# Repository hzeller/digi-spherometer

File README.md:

A Digital Spherometer
=====================

Converting the sagittal measurement (SAG) from a dial indicator and converting
in your head to a sphere radius is a pain.

This project uses a microcontroller to make this more pleasent: it reads out
the digital indicator and converts the reading to a sphere radius value
printed on an OLED display. It also adds some other nifty features, such as
converting this into the ƒ/N for your mirror size. See [firmware]-page for
feature details.

The microcontroller is an [ATTiny85], the display is a 0.96" [SSD1306], or
1.3" [SH1106] compatible 128x64 OLED display with I²C interface.

Supported dial indicators are [Mitutoyo 543] (good, industry-standard quality)
and a generic [autoutlet-indicator] (relatively cheap, has 1μm resolution but
no documented accuracy figures. Sells under many different names).

The [case](./frame) to hold the dial indicator, microcontroller+display and
batteries is 3D-printed, the base can be laser-cut or machined from some metal
plate.

### Quicklinks

Case | Electronics | Firmware | Calibration
-----|-------------|----------|-------------
 |  |  | 

### User Manual

Like any Spherometer, we first need to zero the device on a reference surface.
Typically this is done on a flat surface plate, so this spherometer allows for
that: place it on a flat surface and set the dial indicator to zero.

Unlike other spherometers, this device also allows for another (experimental)
mode: using the grinding tool as a reference surface. The convex shaped tool
has the same (but inverted) curvature as the mirror, so this can be used
as a reference, if the tool and mirror are already sufficiently mated. The
spherometer then can do the math to derive the value from that.

To use that mode, place the spherometer on the tool (make sure the balls and
indicator rest on the tiles not hitting a seam), and zero the dial indicator.
The arrow-shaped button the right side of the display allows to toggle between
the reference mode. The selected mode is highlighted.

Reference on Surface Plate         | Reference on Tool               |
-----------------------------------|---------------------------------|
  | 

The tool reference is probably a bit less accurate, but it does not require
you to be in posession of a flat surface plate.

After the device is zeroed, place it on the mirror. It now shows all relevant
values on one screen. This is what you see from top to bottom:

 * The ƒ/N value for a given mirror size. The mirror size (chosen here: `⌀8"`)
   can be cycled through from a list with the arrow-button.
 * The focal length including error margins derived from dial-indicator error
   and spherometer leg-radius error.
 * The radius is shown in a large font

On the bottom left you see a symbol indicating which reference surface this
was against. There are two symbols indicating flat surface and tool referenced
(same symbols as used in the zero screen).

Millimeter | Inch |
-----------|------|
 | 

So in this example we see in one screen, that this is a mirror with a radius
of about 2482mm, a focal length of 1241mm which is ƒ/6.11 for this
8" mirror. The reference surface was a flat surface plate.

Switching between metric and inch on the dial indicator automatically
switches the calculated values to the corresponding units.

The device does not need an additional power button: it auto-detects
when the drop-indicator is switched off and goes to sleep.

[attiny85]: https://www.microchip.com/wwwproducts/en/ATtiny85
[ssd1306]: https://www.ebay.com/sch/i.html?_nkw=ssd1306+i2c+128x64
[sh1106]: https://www.ebay.com/sch/i.html?_nkw=sh1106+i2c+128x64
[Mitutoyo 543]: https://www.mitutoyo.com/products/small-tool-instruments-and-data-management/indicators/digimatic-indicators/absolute-digimatic-indicator-id-s/
[autoutlet-indicator]: https://www.amazon.com/gp/product/B07C63VFN3
[avr-gcc]: https://gcc.gnu.org/wiki/avr-gcc
[firmware]: ./firmware/README.md

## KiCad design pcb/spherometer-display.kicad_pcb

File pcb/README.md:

Electronics
===========

Schematic is pretty straightforward, mostly things are wired up directly
to the Attiny85. Level conversion of the 1.5V signals from the indicator is
done with some generic NPN transistors.

Some dial indicators, such as Mitutoyo, already have an open collector output,
in that case, the jumpers allow to directly connect the device. The
`R1`, `R2`, `Q1`, `Q2` components need not be populated in that case.

There are two slot connectors on the board, on one side to connect the indicator
(GND, CLK and DATA and optional 1.5V), the other to connect the battery. The
placement is in accordance with the 3D-printed cases.
The connectors are slots to allow for a convenient, low-profile soldering of
wires to it (wires vanish completely inside the slots).
At the top there is some space for easier wire-management (see picture below).

Some indicators (such as the autoutlet) can be powered from an external 1.5V
source; if the battery-pack is tapped in the middle, this is passed through.
Do not use at this point, leave the 1.5V slots disconnected: turns out that the
long battery wire and the connection to the μC injects too much noise. Might
need some filtering.

The board is designed with cut-outs to stay clear of components on the
particular display module I was using to place the board with no gap on the
module; YMMV.

### BOM

Count  | Part                     | Footprint          | Designators  | Remarks
-------|--------------------------|--------------------|--------------|---------
1      | Attiny85V-10             | SOIC-8 5.3mm wide  | U1           |
1      | Capacitor 100n           | 0603 (1608 Metric) | C1           |
3      | Resistor 47k             | 0603 (1608 Metric) | R1, R2, R3   |
2      | MMBTA06LT1HTSA1          | SOT23              | Q1, Q2       | Any SOT23 NPN will do
1      | Panasonic EVQ-P7L01P     | (custom)           | SW1          |
1      | SH1106 Display (i2c)     | (custom)           | Disp         |

Then of course a 1.3" SH1106 module with I²C interface. Make sure the pins
come in sequence `SDA`, `SCL`, `VCC`, `GND` if looked from the back.

### Schematic

### PCB
This board is soldered to the back of a 1.3" OLED display

Also [shared here on OshPark](https://oshpark.com/projects/MvLMlrob); to keep
things thin, order with 0.8mm thickness.

### View through acrylic bottom

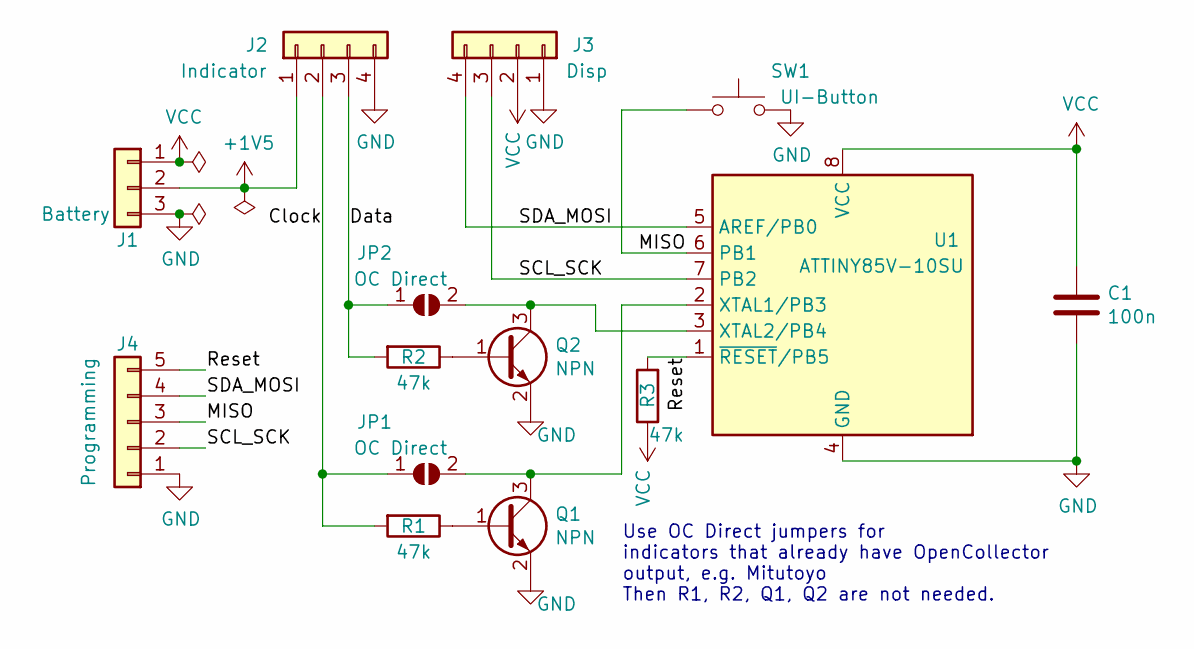
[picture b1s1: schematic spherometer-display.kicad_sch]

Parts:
C1: 100n; C_0603_1608Metric
J1: Battery; connect-edge-3slot-2mm
J2: Indicator; connect-edge-4slot-2mm
J3: Disp; PinHeader_1x04_P2.54mm_Vertical
J4: Programming; PinHeader_1x05_P2.54mm_Vertical
JP1, JP2: OC Direct; SolderJumper-2_P1.3mm_Open_RoundedPad1.0x1.5mm
Q1, Q2: NPN; SOT-23
R1, R2, R3: 47k; R_0603_1608Metric
SW1: UI-Button; EVQP7-Switch
U1: ATTINY85V-10SU; SOIC-8_5.23x5.23mm_P1.27mm

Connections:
+1V5: J1.2, J2.1
/Clock: J2.2, JP1.1 (A), R1.2
/Data: J2.3, JP2.1 (A), R2.2
/MISO: J4.3, SW1.2, U1.6 (PB1)
/Reset: J4.5, R3.2, U1.1 (~RESET/PB5)
/SCL_SCK: J3.3, J4.2, U1.7 (PB2)
/SDA_MOSI: J3.4, J4.4, U1.5 (AREF/PB0)
GND: C1.2, J1.3, J2.4, J3.1, J4.1, Q1.2 (E), Q2.2 (E), SW1.1, U1.4 (GND)
unnamed: JP1.2 (B), Q1.3 (C), U1.2 (XTAL1/PB3)
unnamed: JP2.2 (B), Q2.3 (C), U1.3 (XTAL2/PB4)
unnamed: Q1.1 (B), R1.1
unnamed: Q2.1 (B), R2.1
VCC: C1.1, J1.1, J3.2, R3.1, U1.8 (VCC)

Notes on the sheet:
Use OC Direct jumpers for indicators that already have OpenCollector output, e.g. Mitutoyo Then R1, R2, Q1, Q2 are not needed.

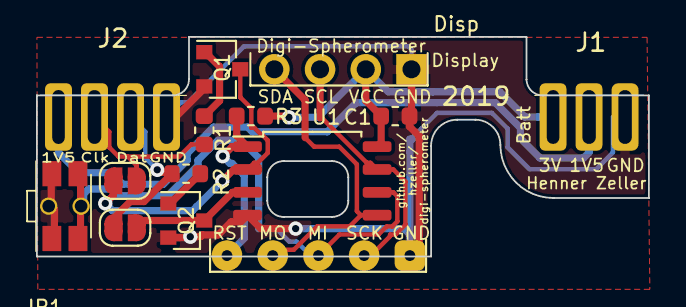
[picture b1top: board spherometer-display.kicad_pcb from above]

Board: 2 copper layers, 34.0 x 12.2 mm, 14 parts (0 on the bottom side), 13 nets.

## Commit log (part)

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2019-02-23 Basic support for ssd1306 display with compiled-in fonts.
    o Provide a i2c master that works with ATTiny devices.
    o initialize SSD1306 display and allow to write blocks from
    PROGMEM. There is not enough space for a full frame-buffer
    in the ATTiny.
    o some basic generated compiled-in font in PROGMEM; generated
    from some BDF font.
2019-02-24 Provide a ClearScreen();
2019-02-24 Document that SSD1306 can deal with faster data rate.
2019-02-24 Read sag from digital gauge and output radius. First version.
    o Dial gauge uses a very simple serial clock/data protocol transmitting
    24 bits. First 20 bits are the value followed by a sign bit. Last
    bit is a non-metric flag.
    o Reading that and also doing some simple 'gauge is off' detection
    which kicks in when the clock stops transmitting (data is sent
    about 10 times/second)
2019-02-24 Update missing glyphs for updated UI. Add sleep mode on indicator off.
    o Update needed characters in fonts for all necessary elements of the UI.
    o When we detect the dial indicator stop clocking data (i.e. it is
    switched off), go to sleep. We still draw about 10μA, but that is
    mostly due to the OLED display. Disconnecting the OLED from GND
    makes current consumption drop to 0.8μA. Maybe add another transistor
    to disconnect OLED ?
2019-02-24 Be more conservative waiting for display power on.
    Waiting 100ms does not seem to work well for a slow ramping up
    power source. Make that 500ms.
    Also provide a Reset() function to reset display after sleep.
2019-02-24 Clean up header.
2019-02-24 Start README.
2019-02-24 Add .gitignore
2019-02-24 Image: Showing the system 'on the bench'
2019-02-25 Move "OK" characters into separate font; add ƒ character to smalltext.
    o The OK characters were forcing the array size for all fonts to be very big,
    so separating that out makes the bignumber font use a lot less memory.
    o add ƒ character to smalltext; want to use it for some focal length display.
2019-02-26 Move dial indicator reading to inline definition in include file.
2019-02-26 Round value instead of truncating.
2019-02-26 Round values. Make things const where possible. Fix indentation.
2019-02-26 Prepare data for ƒ page. Uses more memory, but not pressing right now.
2019-02-26 Simplify interface: have strfmt() format into a statically allocated buffer.
    Instead of passing a buffer to the strfmt() call, have it use some statically
    allocated internal buffer. Of course, this limits the use to a single
    format at a time ... but that is anyway what we're doing :)
    This increases readability (less parameters to pass) and is totally
    fine for this embedded use-case.
    Also saves 8 bytes of code :)
2019-02-26 Add a page that shows focal lengths and ƒ-number for selected mirror sizes. Choose with button.
    A button allows to rotate between three pages: the regular page showing the radius and
    two pages showing the focal lengths (=radius/2) and a choice of ƒ-numbers calculated
    for common mirror sizes. We show 6 different mirror sizes on two pages.
    Also here, we support metric and imperial, depending on the dial setting.
    Choice of metric sizes is {150mm, 200mm, 250mm, 300mm, 400mm, 600mm}, and
    the corresponding imperial sizes are {6", 8", 10", 12", 16", 20"}.
2019-02-26 FillEndOfStripe() is now functionally more a FillStripeRange(). Rename.
2019-02-27 Allow for 'wiggle' room for 'flat'.
    Sometimes the dial will hover around zero +/- 1 count. Let's just
    assume this to be flat.
    Also, rename the reading, the 'value', to 'abs_value' to better
    reflect the range we expect.
2019-02-28 SSD1306: compile time choice if upside down.
2019-03-01 Add a screw-on battery lid.
2019-03-01 Add embedded nuts in print.
2019-03-01 Add prototype pictures in README.
2019-03-03 Add laser-cut pattern for the leg-holding acrylic base.
2019-03-03 Get rid of the display base. We let the bottom transparent.
2019-03-03 Add schematic.
2019-03-08 Make a 'wiggly' battery back. Looks nicer, but also harder to print.
2019-03-09 Add nut-channels everywhere, so that they can be put in after the print.
    Also: add README and Makefile in frame/ directory.
2019-03-09 Move development picture to the firmware README.
2019-03-09 Less text on main-README, point to firmware README for details.
2019-03-10 Add a battery pictogram in the battery box.
2019-03-10 Add git-hash print to hidden part of 3D print (for easier later re-print).
    To be able to re-print a part with exactly the given version, add a
    git-hash number and date of the *.scad file in the final output model.
2019-03-10 Add center mount hole to the base-plate. Update images.
2019-03-11 Add a champfer on the top right/left edges of the Battery box.
    Also add a couple of TODOs. Remove the sideways channel for the cable,
    it should go down the back for easier routing.
2019-03-12 Cable management: run indicator data lines on the back.
2019-03-13 Move git-hash from bottom to inside; simplify top clearance.
    The bottom should be as flat as possible for mounting, and we only
    need the git-hash when re-printing something, so inside is perfectly
    good.
2019-03-13 Add groove for 1.5V cable.
2019-03-13 Make top cut-out a bit more 'organic' with a cos()-swing.
2019-03-15 First hacky way to add display holder..
2019-03-16 Fix todo: use display_high parameter properly.
    Also: add secondary front-edge champfer.
2019-03-16 switch off wiggle-back by default (hard to print)
2019-03-22 Code reduction: make I2C master just a bunch of static methods.
2019-03-30 Swap clk/data in new board. Do pull-up inside.
2019-03-30 Hack in support for SH1106; needs cleanup.
2019-03-30 Shorten splash-screen to fit with wider fonts.
2019-03-31 Move DISP_SH1106 define to Makefile.
    Also, somewhat unrelated, make UTF8 iterator only require prefix++.
2019-03-31 Update prototype image.
2019-03-31 back bottom mounting hole: put nut in from top not battery case.
2019-04-02 Only use SH1106 subset of OLED functionality: more compatible.
2019-04-02 Factor out common calls in SH1106 display to save code.
2019-04-02 Add missing image.
2019-04-05 Widen battery wire hole. Fix indentation.
2019-04-05 Make mounting hole through squeeze-block optionsl.
2019-04-06 Make cable-channels more configurable.
    o Bottom clearance.
    o distance from center.
    o width.
2019-04-08 Adjust display box to fit current larger display.
2019-04-21 Fix relative include to generating stl files.
2019-04-21 Update schematic picture.
2019-04-28 Prepare to be usable with dial indicators that already provide OpenCollector output.
    Add a solder-jumper that allows to directly wire the indicator directly to Attiny.
2019-04-28 Route board; add Makefile to create fab files.
2019-04-28 Update renderings.
2019-04-28 Make bounding box around programming header more compact.
2019-04-28 Re-add OSHW symbol (it got lost as it was not locked).
2019-05-07 Fix: Attiny85 is the huge 5.3mm SOIC-8 footprint.
2019-05-08 Update PCB rendering with larger SOIC-8 footprint that the Attiny has.
2019-05-09 Add EVQP7 switch. It is more sturdy than EPAV.
2019-05-10 Connect indicator and battery with low-profile slot cable solder connects.
2019-05-11 Some cleanup. Also add cut-outs to clear components on SH1106 display back.
2019-05-11 DFM: Add fillets to inner cut-out
2019-05-11 Put programming header legend also on back of board.
2019-05-11 Clarify required pin-sequence of SH1106.
2019-05-11 Un-hide signal layers.
2019-05-11 OshPark uses 1.73mm mill for inner cut-outs; so use 0.9mm radius for shape.
2019-05-16 Adapt case to new PCB. This involves an integrated button.
2019-05-16 Update rendering.
2019-05-16 Remove display side-screws.
2019-05-16 Update case rendering.
2019-05-17 Add ajdustment knob how close the display-case comes to edge.
2019-05-17 Experiment with inverse font display (not for now, display goes dim)
    Other than that: smallish
    o Use diameter symbol for mirror diameter. Not sure if good yet.
    o make sure display is clear-screened when re-switching on the
    indicator while the 'outro' is still shown.
2019-05-17 Align ƒ= text with r= text.
2019-05-17 Update firmware documentation readme.
2019-05-20 Update list of generated fab files.
2019-05-20 Update PCB image.
2019-05-21 Update display image.
2019-05-21 Include UI image in firmware README.
2019-05-21 Slightly nicer crop for oled.
2019-05-21 Left align N-number; provide a little more space for aperture size.
2019-05-23 Link to README.md's directly instead of directories.
    This is more mobile-friendly.
2019-05-25 Make radius a -D-efinable parameter.
2019-05-25 Add calibration description.
2019-05-25 Add a sample calibration scan.
2019-05-25 Add link to calibration page.
2019-05-26 Add more options how to calibrate.
2019-05-26 Make tactile dome poke out a little more.
2019-06-01 Add a tool reference mode.
    When zero-ing, we now can choose between a flat surface and 'tool reference'.
    In tool reference mode, we zero the spherometer while standing on the tool,
    then we can measure the mirror relative to that tool. Advantage is, that there
    is no reference flat surface plate needed: just all the parts alreaday available
    can be used.
    This requires that the tool already has acquired the same shape as the mirror
2019-06-02 Add ball-feet correction.
    (Not sure yet if the math works out for tool-referenced, need to
    have another look).
2019-06-02 Make symbol for flat-reference vs. tool reference a little more distinguishable.
2019-06-03 Introduce error propagation to show expected error on focal length.
    o Introduce simple class ErrorFloat that represents a floating point
    number with error margins. Define operations +, * and /
    o Represent spherometer radius as such value with an error margin of
    0.1mm (compile time parameter)
    o Instead of fiddling with raw values in main, have the dial indicator
    reader functions already converter their value to an ErrorFloat, in
2019-06-03 Fix typo in feet-radius error #define macro.
2019-06-04 Move user-manual out of firmware to toplevel page.
    Include description of new tool-referenced feature.
2020-01-18 Put display in BOM.
2020-01-18 Save a few bytes: setting pullups/DDR in Init can be done with Enable()
2020-01-18 Make button input also subtle indicator if we're in sleep mode.
2020-01-21 For all mirror and lens making: allow convex measurements.
2020-01-23 Use correct digit shifting for imperial Mitutoyo readout.
2021-01-10 Move attiny-specifics out of the i2c-master header.
2021-01-11 Add an implementation of i2c using TWI for chips that support it.
    Provide some commented out section in the Makefile to see how to
    enable it.
2022-08-14 Update to current KiCAD
2022-08-14 Choose compiler that produces the smallest code size.
2022-08-14 Fix paths to 3D models.
2022-11-13 More size optmization flags.
2022-11-13 Name leg distance better. Reduce runtime calculations.
2022-11-13 Make pcb makefile work on nix.
2022-11-18 Make it possible to choose both convex measure + tool reference.
    They might be confusing for too many options in the UI, but can be
    useful for power-users.
2023-02-04 Provide a little host program to test calculation locally.
2023-02-04 Clarify concave/convex
2023-02-05 Clarify negative reading -> concave mirror assumption.
2023-02-05 Refine some comments.
2023-02-05 Makefile dependencies: make more complete.
2023-05-23 Champfer'ed front. Screws from the battery compartment.
2023-05-28 Some tweaks.
2023-08-10 Adapt fab script to latest kicad.
2024-11-28 There is no gcc8 packaged anymore. Use gcc13.
    Unfortunately, newer gccs often use more space, but looks like we're
    good for now.

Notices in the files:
pcb/spherometer-display.kicad_pcb:
© 2019 CC-BY-SA
